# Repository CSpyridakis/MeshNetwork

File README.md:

[HPY411] Embedded Systems

#Directories

Milestone Reports and Presentation: reports/

Eagle Schematics: Eagle/Embedded/NodeBoard/

Eagle Dependencies: Eagle/dependencies

Arduino / Esp8266 Dependencies: ESP8266_Dependencies/
 
Code: WSN/

Arduino-ESP8266 Dependencies: dependencies/

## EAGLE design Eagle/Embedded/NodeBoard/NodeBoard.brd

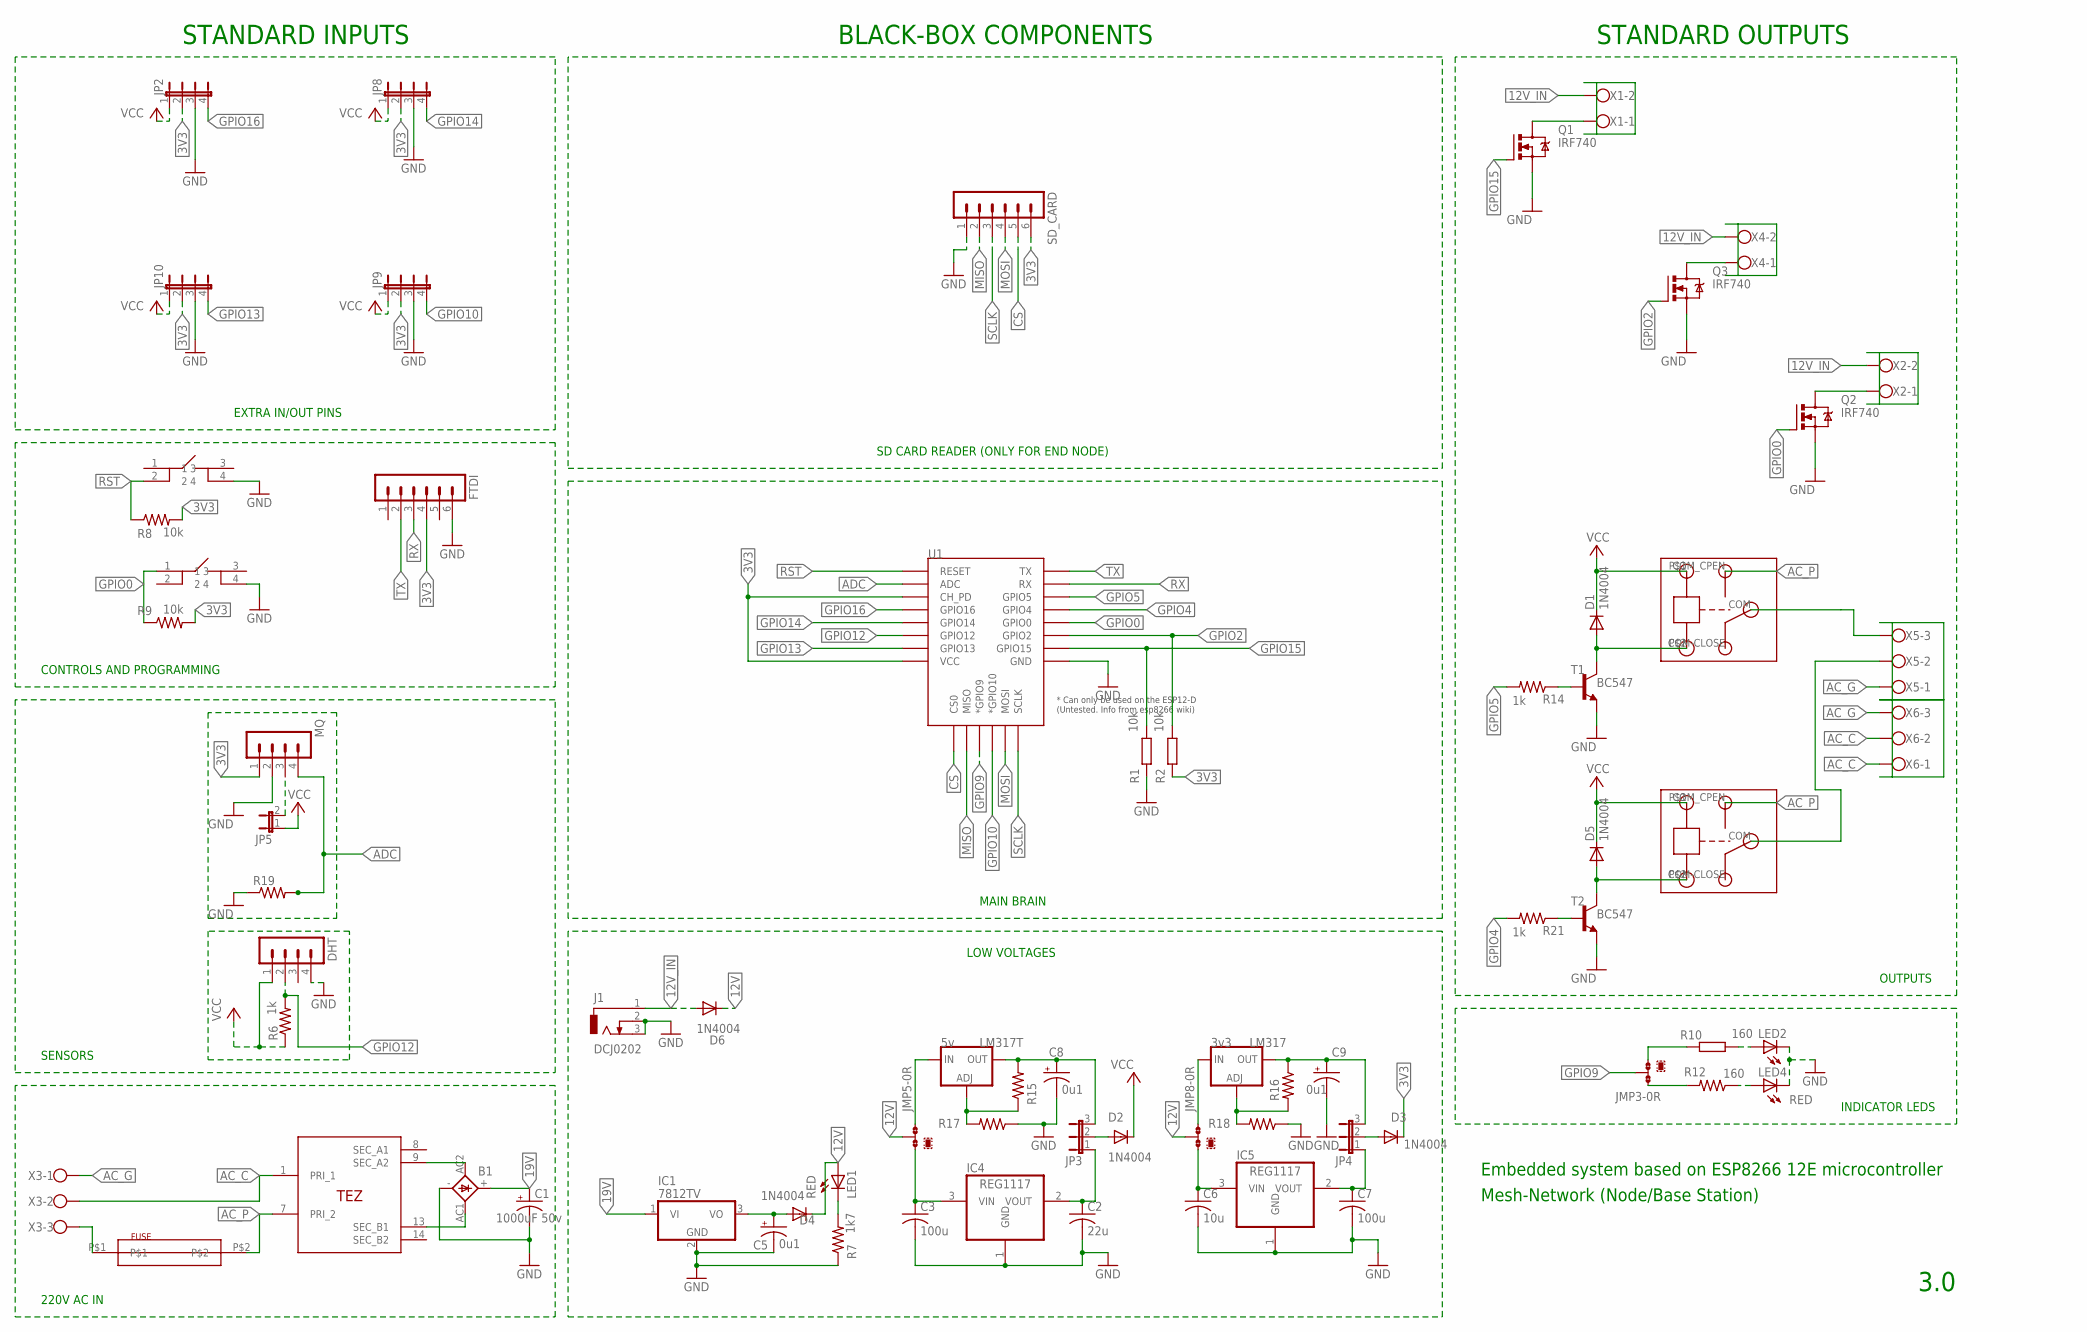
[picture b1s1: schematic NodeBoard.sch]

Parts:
B1: KBL
C1: 1000uF 50v; E5-13
C2: 22u; C0805
C3, C7: 100u; C0805
C5, C8, C9: 0u1; E2,5-6E
C6: 10u; C0805
D1, D2, D3, D4, D5, D6: 1N4004; DO41-10
DHT: MA04-1
FTDI: MA06-1
IC1: 7812TV; TO220V
IC4, IC5: REG1117; SOT223
J1: DCJ0202
JMP3, JMP5, JMP8: 0R-JUMPA; A0R-JMP
JP2, JP8, JP9, JP10: JP4E; JP4
JP3, JP4: JP2E; JP2
JP5: JP1E; JP1
LED1, LED4: RED; LED5MM
LED2: LEDCHIPLED_1206; CHIPLED_1206
LM317: 3v3; 317TS
LM317T: 5v; 317TS
MQ: MA04-1
Q1, Q2, Q3: IRF740; TO220BV
R1, R2: 10k; R0603
R6, R14, R21: 1k; 0204/7
R7, R16, R18: 1k7; 0204/7
R8, R9: 10k; 0204/7
R10: 160; R0603
R12: 160; 0204/7
R15: 15k; 0204/7
R17: 28k; 0204/7
R19: R-US_0204/7; 0204/7
SD_CARD: MA06-1
T1, T2: BC547; TO92
U1: ESP12ESMD; ESP12E-SMD
U$1, U$4: RELAY
U$2: TEZ_16THROUGH_HOLE; TEZ_16
U$3: FUSE_24X11THROUGH_HOLE; FUSE_24X11
U$5, U$6: TACT_SWITCHTHROUGH_HOLE; TACT_SWITCH_TH
X1, X2, X4: W237-102
X3, X5, X6: W237-103

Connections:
3V3: D3.C, FTDI.4, JP2.2, JP8.2, JP9.2, JP10.2, MQ.1, R2.1, R8.2, R9.2, SD_CARD.6, U1.CH_PD, U1.VCC
12V: D4.C, D6.C, JMP5.2, JMP8.2, LED1.A
12V_IN: D6.A, J1.1, X1.2, X2.2, X4.2
19V: B1.+, C1.+, IC1.1 (VI)
AC_C: U$2.1 (PRI_1), X3.2, X6.1, X6.2
AC_G: X3.1, X5.1, X6.3
AC_P: U$1.COM_CPEN (COM-OPEN), U$2.7 (PRI_2), U$3.P$2, U$4.COM_CPEN (COM-OPEN)
ADC: MQ.4, R19.2, U1.ADC
CS: SD_CARD.5, U1.CS0
GND: B1.-, C1.-, C2.2, C3.2, C5.-, C6.2, C7.2, C8.-, C9.-, DHT.4, FTDI.6, IC1.2 (GND), IC4.1 (GND), IC5.1 (GND), J1.2, J1.3, JP2.3, JP8.3, JP9.3, JP10.3, LED2.C, LED4.K (C), MQ.2, Q1.S, Q2.S, Q3.S, R1.1, R7.1, R17.1, R18.1, R19.1, SD_CARD.1, T1.1 (E), T2.1 (E), U1.GND, U$5.4, U$6.4
GPIO0: Q2.G, R9.1, U1.GPIO0, U$6.1
GPIO2: Q3.G, R2.2, U1.GPIO2
GPIO4: R21.2, U1.GPIO4
GPIO5: R14.2, U1.GPIO5
GPIO9: JMP3.2, U1.GPIO9 (*GPIO9)
GPIO10: JP9.4, U1.GPIO10 (*GPIO10)
GPIO12: DHT.2, R6.2, U1.GPIO12
GPIO13: JP10.4, U1.GPIO13
GPIO14: JP8.4, U1.GPIO14
GPIO15: Q1.G, R1.2, U1.GPIO15
GPIO16: JP2.4, U1.GPIO16
MISO: SD_CARD.2, U1.MISO
MOSI: SD_CARD.4, U1.MOSI
unnamed: B1.AC2 (AC1), U$2.9 (SEC_A2)
unnamed: LED1.K (C), R7.2
unnamed: B1.AC1 (AC2), U$2.13 (SEC_B1)
unnamed: U$1.COM, X5.3
unnamed: JP5.2, MQ.3
unnamed: Q1.D, X1.1
unnamed: Q3.D, X4.1
unnamed: LED2.A, R10.2
unnamed: LED4.A, R12.1
unnamed: JMP3.1, R12.2
unnamed: JMP3.3, R10.1
unnamed: R14.1, T1.2 (B)
unnamed: D1.A, T1.3 (C), U$1.P$2 (GND)
unnamed: R21.1, T2.2 (B)
unnamed: C8.+, JP3.3, LM317T.2 (OUT), R15.2
unnamed: LM317T.1 (ADJ), R15.1, R17.2
unnamed: C9.+, JP4.3, LM317.2 (OUT), R16.1
unnamed: LM317.1 (ADJ), R16.2, R18.2
unnamed: JMP5.3, LM317T.3 (IN)
unnamed: JMP8.3, LM317.3 (IN)
unnamed: D2.A, JP3.2
unnamed: D3.A, JP4.2
unnamed: C5.+, D4.A, IC1.3 (VO)
unnamed: C2.1, IC4.2 (VOUT), JP3.1
unnamed: C6.1, IC5.3 (VIN), JMP8.1
unnamed: C3.1, IC4.3 (VIN), JMP5.1
unnamed: Q2.D, X2.1
unnamed: C7.1, IC5.2 (VOUT), JP4.1
unnamed: D5.A, T2.3 (C), U$4.P$2 (GND)
unnamed: U$3.P$1, X3.3
unnamed: U$4.COM, X5.2
RST: R8.1, U1.RESET, U$5.2
RX: FTDI.3, U1.RXD0 (RX)
SCLK: SD_CARD.3, U1.SCLK
TX: FTDI.2, U1.TXD0 (TX)
VCC: D1.C, D2.C, D5.C, DHT.1, JP2.1, JP5.1, JP8.1, JP9.1, JP10.1, R6.1, U$1.P$1 (IN), U$4.P$1 (IN)

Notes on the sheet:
220V AC IN
CONTROLS AND PROGRAMMING
SENSORS
3.0
Embedded system based on ESP8266 12E microcontroller
LOW VOLTAGES
INDICATOR LEDS
OUTPUTS
Mesh-Network (Node/Base Station)
EXTRA IN/OUT PINS
SD CARD READER (ONLY FOR END NODE)
MAIN BRAIN
STANDARD INPUTS
STANDARD OUTPUTS
BLACK-BOX COMPONENTS

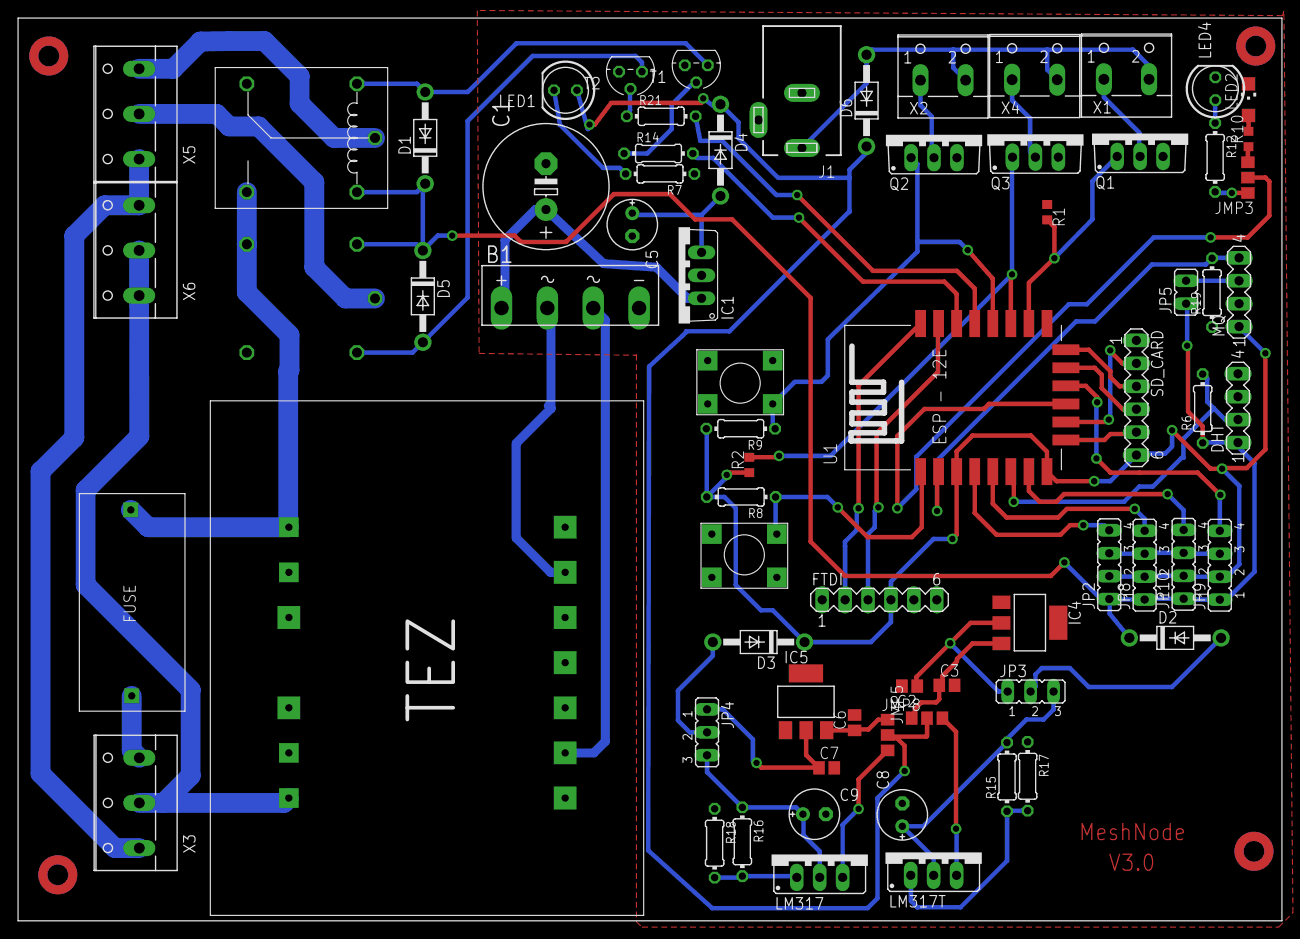
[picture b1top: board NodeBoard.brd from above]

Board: 2 copper layers, 140.0 x 100.0 mm, 71 parts (1 on the bottom side), 59 nets.

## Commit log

2017-09-22 init
2017-09-22 Added documentation
2017-09-24 Added dependencies
2017-09-24 Report added
2017-09-25 DHT data can be distributed successfully
2017-09-26 Added Eagle files
2017-09-26 ESP-12E datasheet added
2017-09-26 Serial print cmds removed
2017-09-26 Serial print cmds removed3
2017-09-26 refresh rate changed
2017-09-26 refresh rate changed2
2017-09-26 Timers OK
2017-09-27 Added all sensors
2017-09-27 All sensors working correctly
2017-09-27 All sensors are correctly calibrated
2017-09-27 Experimenting with WatchDog timers...
2017-09-28 Added os_timer
2017-09-28 Changed timers to os_timer_t
2017-09-28 Cleaning up code and adding documentation
2017-09-28 Cleaning up code and adding documentation2
2017-09-28 Fixed a bug with DHT11 low voltage
2017-09-28 Added flash instructions
2017-09-29 Refactoring.Added an extra timer.Events are produced and consumed on different timers now.
2017-09-29 Trying to fix WiFi connection
2017-09-29 Refactoring.Added an extra timer.Events are produced and consumed on different timers now.2
2017-09-29 Fixed timer callbacks.Removed interrupts.
2017-09-29 Fix2
2017-09-30 Watchdog changes
2017-09-30 timer0 and timer1 added
    Hardware timer0 handles all the broadcast related work
2017-10-01 Added partial documentation in easyMesh.* and *.ino files. Moved #defined constants in myconstants.h file.
2017-10-01 More documentation and code refactoring on easyMesh files.
2017-10-02 Documentation updated.Main loop() now includes checks for interrupts. Threshold values added in meshConstants.h. Added extra image and example log.
2017-10-02 Documentation updated.Main loop() now includes checks for interrupts. Threshold values added in meshConstants.h. Added extra image and example log. Updated proposal.
2017-10-03 Eagle controls and sensors added
2017-10-03 Added relay node option in meshConstants. Migrated the getReadings from the ISR to the main loop() func.
2017-10-03 Fixed initial values on some vars so relay nodes can function properly.
2017-10-03 Fixed a bug on DHT11, now working without any problems.
2017-10-04 Updated easyMesh documentation.
2017-10-04 Various bug fixes.
2017-10-05 Extra documentation
2017-10-05 Documentation update.
2017-10-05 Logs of 4 esp8266 (observed by a relay)
2017-10-27 Eagle files ready for MeshNode
2017-10-27 Minor Eagle Board fixes
2017-10-27 Eagle Flipped directional components
2017-10-27 Eagle via fix
2017-10-27 Fix dimentions
2017-10-27 Eagle 121x96 end dimention
2017-10-30 Eagle pcb v2.0
2017-11-02 Updated report.docx
2017-11-03 Milestone 2
2017-11-03 Milestone 2 reports added. Code refactoring. Deleted dependencies zip file.
2017-11-03 Milestone 2.
2017-11-24 End-point code for esp8266 web server.
2017-12-05 Milestone 3.
2017-12-06 Report, and eagle changes
2017-12-06 Final report added.
2017-12-06 Presentation added.
